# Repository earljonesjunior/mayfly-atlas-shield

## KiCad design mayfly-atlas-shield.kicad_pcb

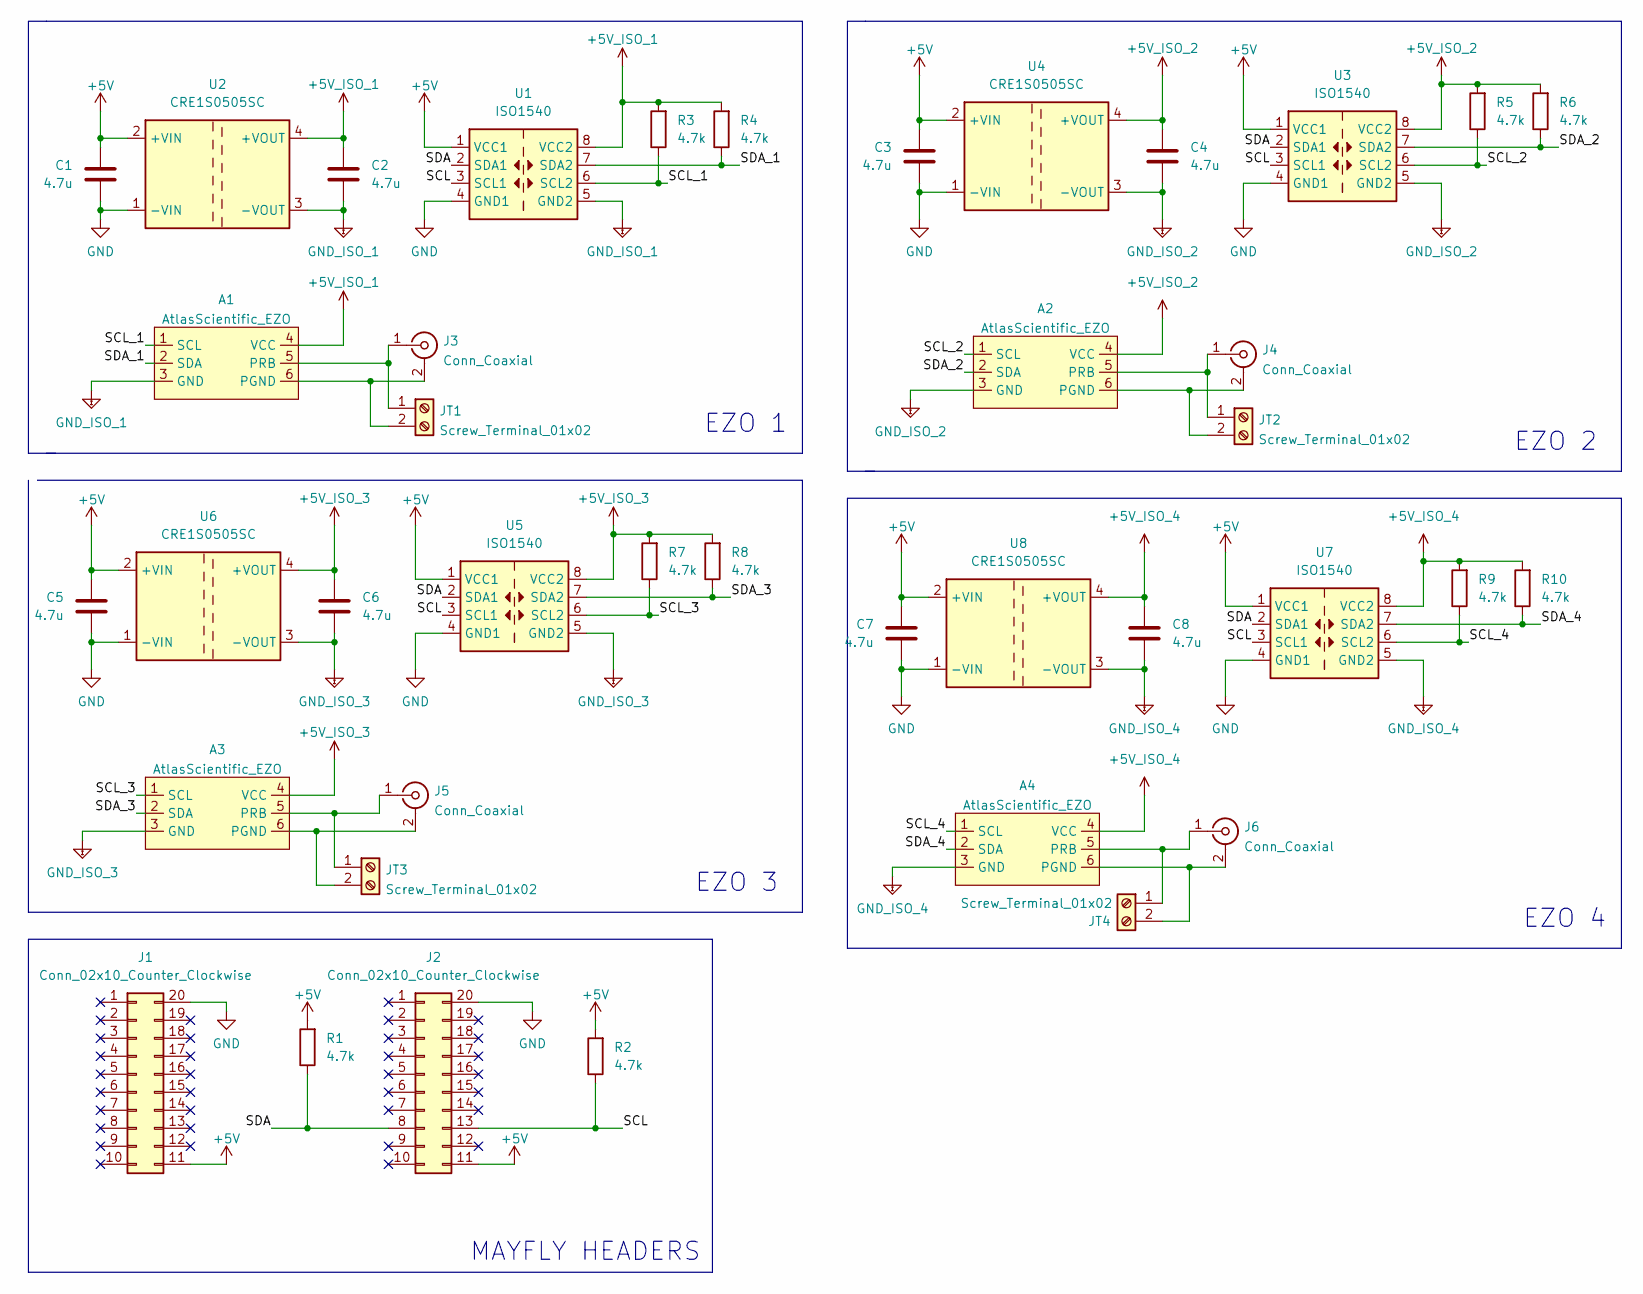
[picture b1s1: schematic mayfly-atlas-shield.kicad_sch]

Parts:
A1, A2, A3, A4: AtlasScientific_EZO
C1, C2, C3, C4, C5, C6, C7, C8: 4.7u; C_0805_2012Metric
J1, J2: Conn_02x10_Counter_Clockwise; Mayfly_v1_Headers
J3, J4, J5, J6: Conn_Coaxial; SMA_Amphenol_132134-16_Vertical
JT1, JT2, JT3, JT4: Screw_Terminal_01x02; TerminalBlock_Phoenix_PT-1,5-2-5.0-H_1x02_P5.00mm_Horizontal
R1, R2, R3, R4, R5, R6, R7, R8, R9, R10: 4.7k; R_0805_2012Metric
U1, U3, U5, U7: ISO1540; SOIC-8_3.9x4.9mm_P1.27mm
U2, U4, U6, U8: CRE1S0505SC; Converter_DCDC_Murata_CRE1xxxxxxSC_THT

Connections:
+5V: C1.2, C3.2, C5.2, C7.2, J1.11, J2.11, R1.2, R2.2, U1.1 (VCC1), U2.2 (+VIN), U3.1 (VCC1), U4.2 (+VIN), U5.1 (VCC1), U6.2 (+VIN), U7.1 (VCC1), U8.2 (+VIN); also elsewhere on the board
+5V_ISO_1: A1.4 (VCC), C2.1, R3.2, R4.2, U1.8 (VCC2), U2.4 (+VOUT)
+5V_ISO_2: A2.4 (VCC), C4.1, R5.2, R6.2, U3.8 (VCC2), U4.4 (+VOUT)
+5V_ISO_3: A3.4 (VCC), C6.1, R7.2, R8.2, U5.8 (VCC2), U6.4 (+VOUT)
+5V_ISO_4: A4.4 (VCC), C8.1, R9.2, R10.2, U7.8 (VCC2), U8.4 (+VOUT); also elsewhere on the board
/SCL: J2.13, R2.1, U1.3 (SCL1), U3.3 (SCL1), U5.3 (SCL1), U7.3 (SCL1)
/SCL_1: A1.1 (SCL), R3.1, U1.6 (SCL2)
/SCL_2: A2.1 (SCL), R5.1, U3.6 (SCL2)
/SCL_3: A3.1 (SCL), R7.1, U5.6 (SCL2)
/SCL_4: A4.1 (SCL), R9.1, U7.6 (SCL2)
/SDA: J2.8, R1.1, U1.2 (SDA1), U3.2 (SDA1), U5.2 (SDA1), U7.2 (SDA1)
/SDA_1: A1.2 (SDA), R4.1, U1.7 (SDA2)
/SDA_2: A2.2 (SDA), R6.1, U3.7 (SDA2)
/SDA_3: A3.2 (SDA), R8.1, U5.7 (SDA2)
/SDA_4: A4.2 (SDA), R10.1, U7.7 (SDA2)
GND: C1.1, C3.1, C5.1, C7.1, J1.20, J2.20, U1.4 (GND1), U2.1 (-VIN), U3.4 (GND1), U4.1 (-VIN), U5.4 (GND1), U6.1 (-VIN), U7.4 (GND1), U8.1 (-VIN); also elsewhere on the board
GND_ISO_1: A1.3 (GND), C2.2, U1.5 (GND2), U2.3 (-VOUT)
GND_ISO_2: A2.3 (GND), C4.2, U3.5 (GND2), U4.3 (-VOUT)
GND_ISO_3: A3.3 (GND), C6.2, U5.5 (GND2), U6.3 (-VOUT)
GND_ISO_4: A4.3 (GND), C8.2, U7.5 (GND2), U8.3 (-VOUT); also elsewhere on the board
unnamed: A1.5 (PRB), J3.1 (In), JT1.1
unnamed: A1.6 (PGND), J3.2 (Ext), JT1.2
unnamed: A2.5 (PRB), J4.1 (In), JT2.1
unnamed: A2.6 (PGND), J4.2 (Ext), JT2.2
unnamed: A3.5 (PRB), J5.1 (In), JT3.1
unnamed: A3.6 (PGND), J5.2 (Ext), JT3.2
unnamed: A4.5 (PRB), J6.1 (In), JT4.1
unnamed: A4.6 (PGND), J6.2 (Ext), JT4.2

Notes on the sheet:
EZO 3
MAYFLY HEADERS
EZO 1
EZO 4
EZO 2

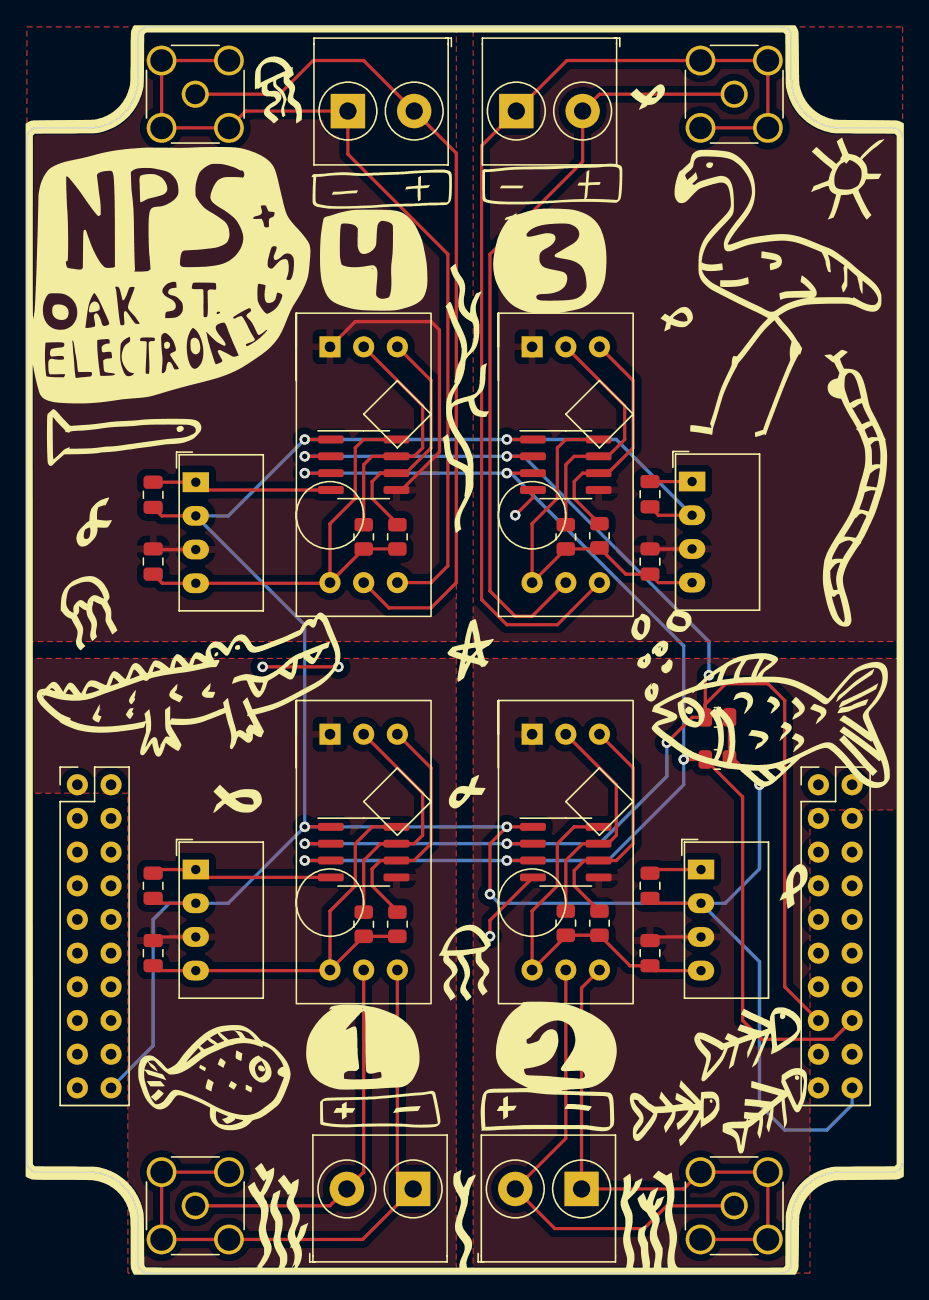
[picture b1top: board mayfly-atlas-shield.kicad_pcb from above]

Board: 2 copper layers, 66.0 x 94.0 mm, 40 parts (0 on the bottom side), 28 nets.

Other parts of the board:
Ue: CRE1S0505SC; Converter_DCDC_Murata_CRE1xxxxxxSC_THT

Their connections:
+5V: Ue.2 (+VIN); also elsewhere on the board
+5V_ISO_4: Ue.4 (+VOUT); also elsewhere on the board
GND: Ue.1 (-VIN); also elsewhere on the board
GND_ISO_4: Ue.3 (-VOUT); also elsewhere on the board

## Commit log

2022-08-07 pre isolator migration
2022-08-08 schematic finished
2022-08-08 Revert "schematic finished"
    This reverts commit 0515e0858473c3025873806ec2f0323e48e731ae.
2022-08-08 Revert "Revert "schematic finished""
    This reverts commit c28a19f90ef5367994c1686424e0fa42ea2641de.
2022-08-08 Merge fix (#1)
    * schematic finished
    * Revert "schematic finished"
    This reverts commit 0515e0858473c3025873806ec2f0323e48e731ae.
    * Revert "Revert "schematic finished""
    This reverts commit c28a19f90ef5367994c1686424e0fa42ea2641de.
    * merge conflict fix
2022-08-13 pcb layout
2022-08-15 initial revision complete
2022-09-03 gerbers
